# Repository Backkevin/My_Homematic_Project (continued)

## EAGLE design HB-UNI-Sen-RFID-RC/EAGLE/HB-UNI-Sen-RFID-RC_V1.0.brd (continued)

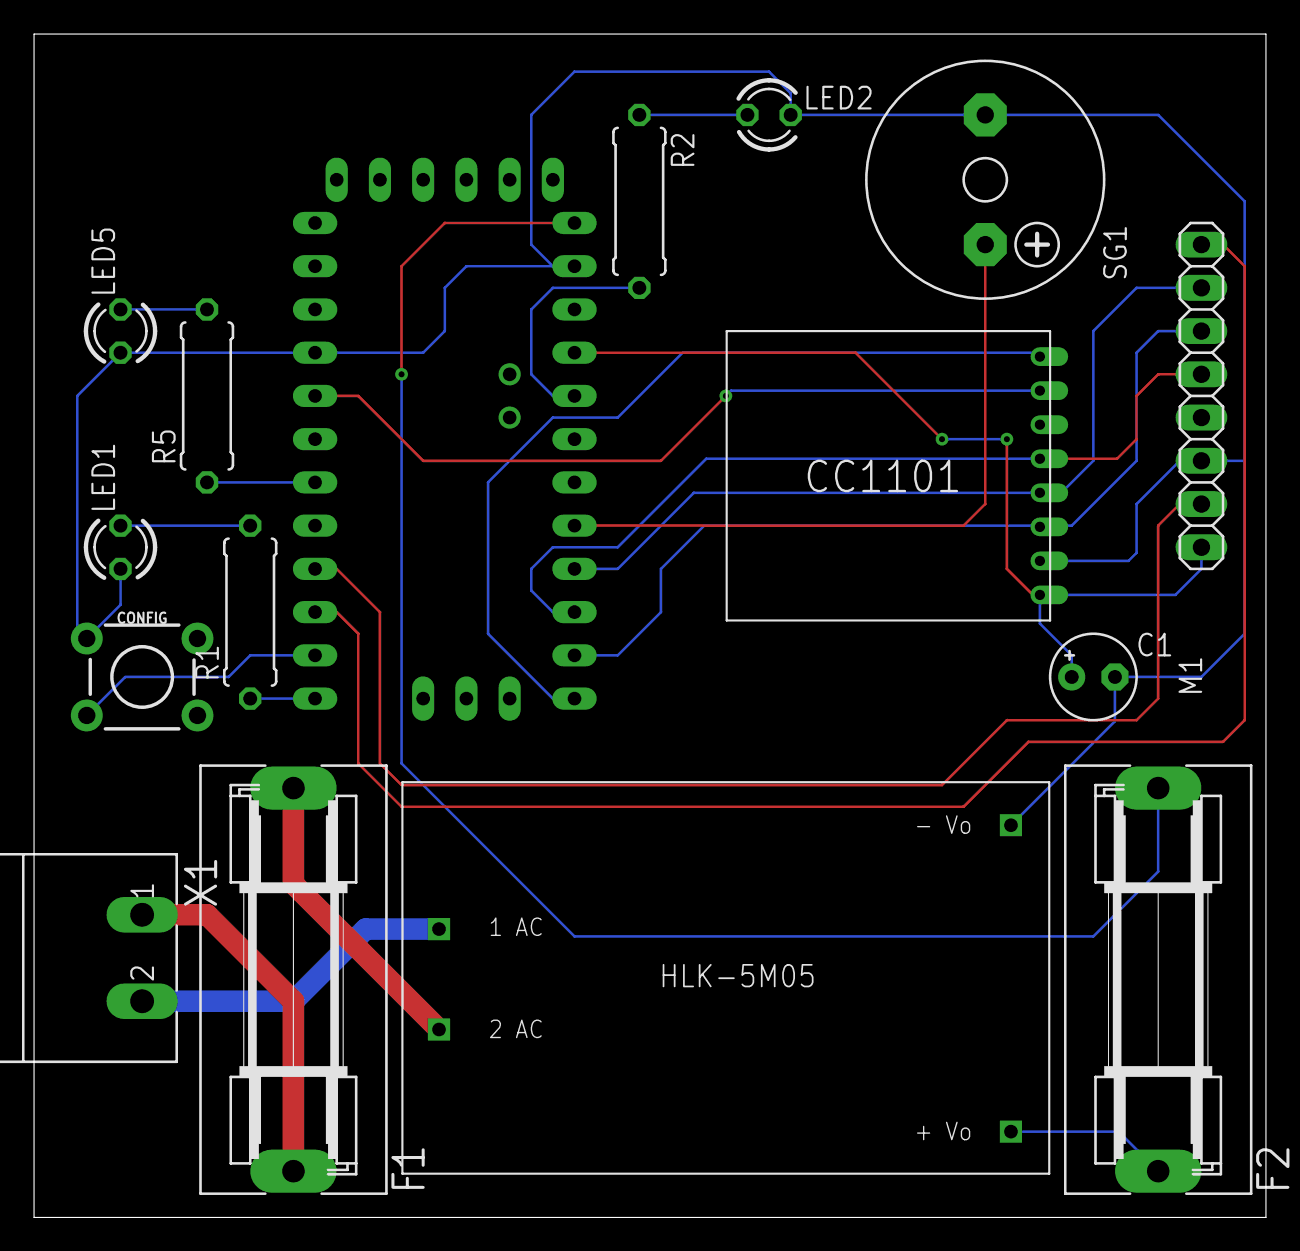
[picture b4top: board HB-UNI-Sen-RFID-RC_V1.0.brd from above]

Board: 2 copper layers, 72.4 x 69.5 mm, 16 parts (0 on the bottom side), 22 nets.

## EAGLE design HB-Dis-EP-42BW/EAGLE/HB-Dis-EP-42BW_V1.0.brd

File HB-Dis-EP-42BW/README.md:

# HB-Dis-EP-42BW
+ HB-Dis-EP-42BW
	+ V1.0
		* Work 50%
		* 230VAC Version
		* Partlist not OK
	+ Work in progress !

### Partslist 230VAC Version
                    
  Part Name   |      PIC      |   Part Info   | Part Quantity |   Part Link 
------------- | ------------- | ------------- | ------------- | -------------
Atmega1284||Atmega1284|1|[Links](https://de.aliexpress.com/item/33055132798.html?spm=a2g0o.productlist.0.0.77eb5e5fPvaMvS&algo_pvid=d8744989-b02e-473b-b5f8-e39dbb865ab2&algo_expid=d8744989-b02e-473b-b5f8-e39dbb865ab2-4&btsid=08f508f2-d514-42dc-8de8-63a7cc07db76&ws_ab_test=searchweb0_0,searchweb201602_2,searchweb201603_52)
CC1101||CC1101 Funkmodul|1|[Links](https://de.aliexpress.com/item/32924239954.html?spm=a2g0s.9042311.0.0.27424c4dO9ofu2)
Config,S1 - S8||Taster 6x6|9|[Links](https://de.aliexpress.com/item/32912263133.html?spm=a2g0s.9042311.0.0.2cb44c4dtuowdv)
LED1,LED2||LED 3mm|2|[Links](https://de.aliexpress.com/item/32844298998.html?spm=a2g0s.9042311.0.0.27424c4dBW9kvr)
HLK-5M05||HLK-PM01|1|[Links](https://de.aliexpress.com/item/32705471039.html?spm=a2g0s.9042311.0.0.2cb44c4dtuowdv)
F1,F2||Sicherungshalter|2|[Links](https://de.aliexpress.com/item/32817849786.html?spm=a2g0o.productlist.0.0.260073beDSkClD&algo_pvid=51b52a6f-dc94-4152-9721-98bffea40076&algo_expid=51b52a6f-dc94-4152-9721-98bffea40076-1&btsid=c94e558f-368d-470b-a49c-61c69230d3d9&ws_ab_test=searchweb0_0,searchweb201602_2,searchweb201603_52)
R1,R2||470 Ohm Widerstand|2|[Links](https://de.aliexpress.com/item/32475181535.html?spm=a2g0o.productlist.0.0.d4fa8034p2AKck&s=p&algo_pvid=4976c9e3-6165-4df4-b127-6d9845fdbe12&algo_expid=4976c9e3-6165-4df4-b127-6d9845fdbe12-1&btsid=7a52ff49-9ff4-47d2-965f-007ad481e8b7&ws_ab_test=searchweb0_0,searchweb201602_2,searchweb201603_52)
230V||Wannenstecker für AKL 249, 2-pol, RM5,08|1|[Links](https://www.reichelt.de/wannenstecker-fuer-akl-249-2-pol-rm5-08-akl-230-02-p36701.html?)
Arduino||Pin Header Streifen 12 Pin|2|[Links](https://de.aliexpress.com/item/32904918519.html?spm=a2g0s.9042311.0.0.27424c4dCsKCBi)
CC1101||Stiftleiste 20 polig, vergoldet, Raster 2,00mm|1|[Links](https://secure.reichelt.com/lu/de/stiftleiste-20-pol-vergoldet-bkl-10120400-p235635.html?)
C1||50V10UF|1|[Links](https://de.aliexpress.com/item/32741687066.html?spm=a2g0o.productlist.0.0.4d225216N68Cr1&algo_pvid=dbcb75f4-e623-4355-8aa4-ccd3a7b65d32&algo_expid=dbcb75f4-e623-4355-8aa4-ccd3a7b65d32-3&btsid=a9b8176e-1372-45d7-a781-8d3fc9fab8e5&ws_ab_test=searchweb0_0,searchweb201602_2,searchweb201603_52)
Arduino||Jumper|1|[Links](https://de.aliexpress.com/item/32873263301.html?spm=a2g0o.productlist.0.0.18ea263dluRsmQ&algo_pvid=b495ebad-e4de-4809-a086-8143c1f9f12b&algo_expid=b495ebad-e4de-4809-a086-8143c1f9f12b-2&btsid=53bb7c29-6fd7-4471-b8c4-bc2766b36d10&ws_ab_test=searchweb0_0,searchweb201602_2,searchweb201603_52)
Display||4,2 zoll color tinte bildschirm RSW|1|[Links](https://de.aliexpress.com/item/32960911279.html?spm=a2g0s.9042311.0.0.27424c4durraPx)
-|-|-|-
OPTIONAL||FT232RL USB zu TTL Serielle Adapter|1|[Links](https://de.aliexpress.com/item/32846166237.html?spm=a2g0s.9042311.0.0.27424c4dQGznlY)

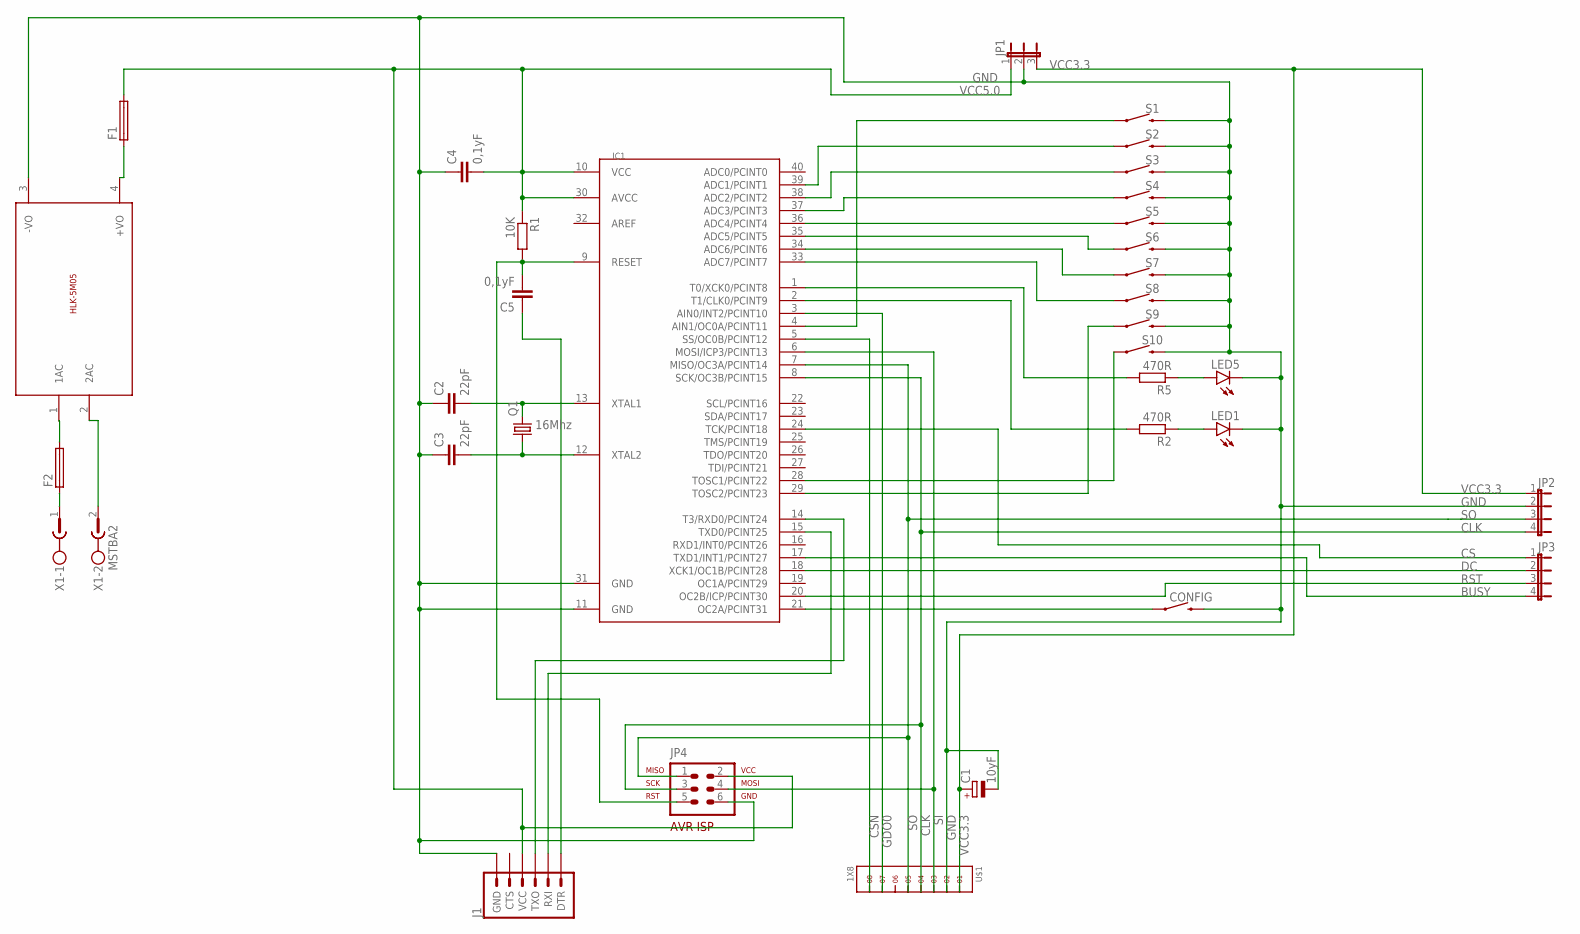
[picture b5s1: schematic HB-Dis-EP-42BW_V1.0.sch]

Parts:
C1: 10yF; E2,5-5
C2, C3: 22pF; C025-024X044
C4, C5: 0,1yF; C025-024X044
CONFIG: MOMENTARY-SWITCH-SPST-PTH-6.0MM-KIT; TACTILE_SWITCH_PTH_6.0MM_KIT
F1, F2: SH22,5A
IC1: MEGA1284P; DIL40
J1: 6_PIN_SERIAL_TARGETLONGPADS; 1X06_LONGPADS
JP1: JP2E; JP2
JP2, JP3: JP4E; JP4
JP4: AVR-ISP-6VERT; AVR-ISP-6
LED1, LED5: LED3MM
Q1: 16Mhz; HC49U-V
R1: 10K; 0309/10
R2, R5: 470R; 0309/10
S1, S2, S3, S4, S5, S6, S7, S8, S9, S10: MOMENTARY-SWITCH-SPST-PTH-6.0MM-KIT; TACTILE_SWITCH_PTH_6.0MM_KIT
U$1: 1X8
U$3: 5VDC/5W; HLK-5M05
X1: MSTBA2

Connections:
BUSY: IC1.17 (TXD1/INT1/PCINT27), JP3.4
CLK: IC1.8 (SCK/OC3B/PCINT15), JP2.4, JP4.3, U$1.4
CS: IC1.24 (TCK/PCINT18), JP3.1
CSN: IC1.5 (SS/OC0B/PCINT12), U$1.8
DC: IC1.18 (XCK1/OC1B/PCINT28), JP3.2
GDO0: IC1.3 (AIN0/INT2/PCINT10), U$1.7
GND: C1.-, C2.1, C3.1, C4.1, CONFIG.3 (2), IC1.11 (GND), IC1.31 (GND), J1.6 (GND), JP1.2, JP2.2, JP4.6, LED1.K (C), LED5.K (C), S1.3 (2), S2.3 (2), S3.3 (2), S4.3 (2), S5.3 (2), S6.3 (2), S7.3 (2), S8.3 (2), S9.3 (2), S10.3 (2), U$1.2, U$3.3 (-VO)
unnamed: C2.2, IC1.13 (XTAL1), Q1.2
unnamed: C3.2, IC1.12 (XTAL2), Q1.1
unnamed: C5.1, J1.1 (DTR)
unnamed: LED1.A, R2.1
unnamed: F2.1, X1.1
unnamed: U$3.2 (2AC), X1.2
unnamed: F2.2, U$3.1 (1AC)
unnamed: F1.1, U$3.4 (+VO)
unnamed: C5.2, IC1.9 (RESET), JP4.5, R1.2
unnamed: IC1.15 (TXD0/PCINT25), J1.2 (RXI)
unnamed: LED5.A, R5.1
unnamed: IC1.4 (AIN1/OC0A/PCINT11), S1.1
unnamed: IC1.14 (T3/RXD0/PCINT24), J1.3 (TXO)
unnamed: IC1.39 (ADC1/PCINT1), S2.1
unnamed: IC1.38 (ADC2/PCINT2), S3.1
unnamed: IC1.37 (ADC3/PCINT3), S4.1
unnamed: IC1.36 (ADC4/PCINT4), S5.1
unnamed: IC1.35 (ADC5/PCINT5), S6.1
unnamed: IC1.34 (ADC6/PCINT6), S7.1
unnamed: IC1.33 (ADC7/PCINT7), S8.1
unnamed: IC1.28 (TOSC1/PCINT22), S10.1
unnamed: IC1.29 (TOSC2/PCINT23), S9.1
unnamed: CONFIG.1, IC1.21 (OC2A/PCINT31)
unnamed: IC1.1 (T0/XCK0/PCINT8), R5.2
unnamed: IC1.2 (T1/CLK0/PCINT9), R2.2
RST: IC1.20 (OC2B/ICP/PCINT30), JP3.3
SI: IC1.6 (MOSI/ICP3/PCINT13), JP4.4, U$1.3
SO: IC1.7 (MISO/OC3A/PCINT14), JP2.3, JP4.1, U$1.5
VCC3.3: C1.+, JP1.3, JP2.1, U$1.1
VCC5.0: C4.2, F1.2, IC1.10 (VCC), IC1.30 (AVCC), J1.4 (VCC), JP1.1, JP4.2, R1.1

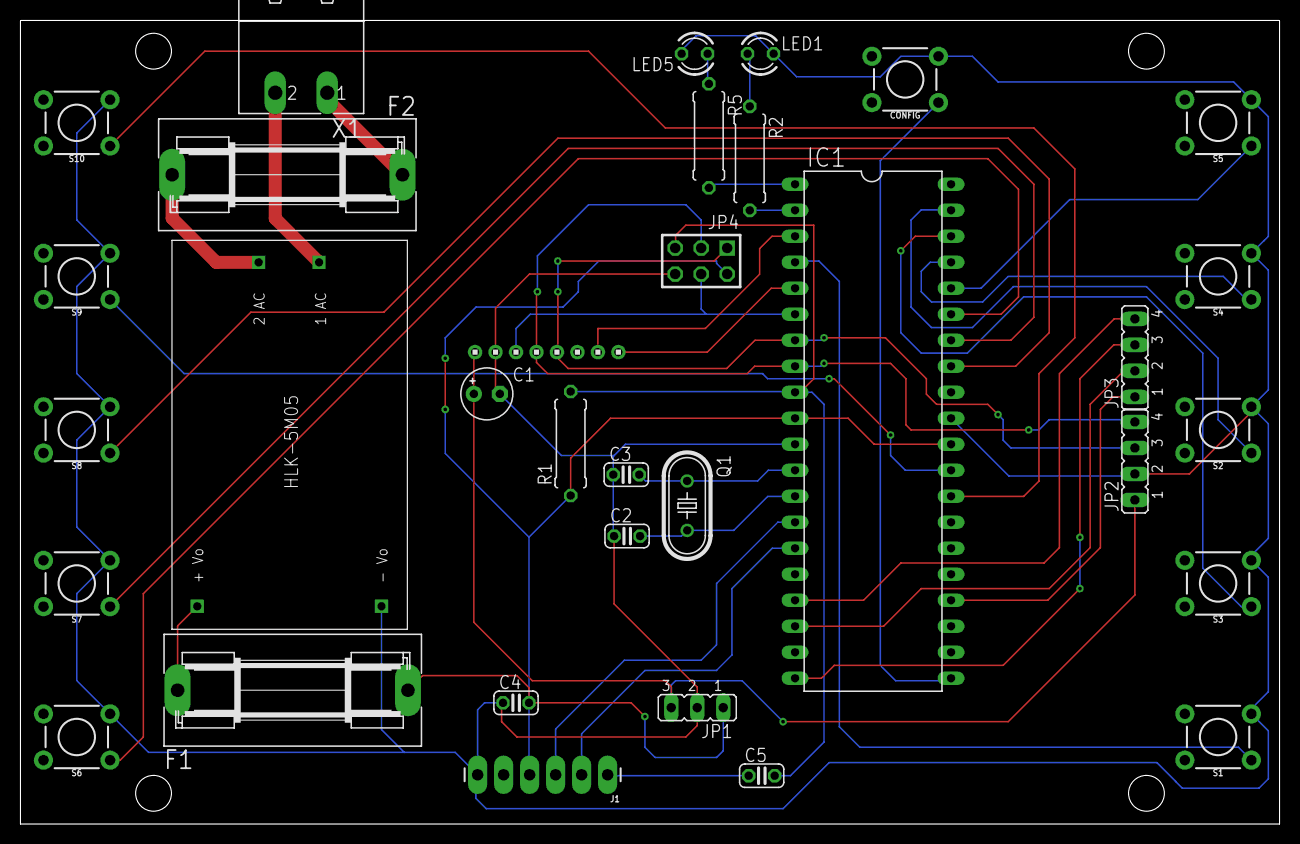
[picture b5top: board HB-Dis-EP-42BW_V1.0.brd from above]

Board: 2 copper layers, 123.0 x 78.5 mm, 33 parts (0 on the bottom side), 37 nets.

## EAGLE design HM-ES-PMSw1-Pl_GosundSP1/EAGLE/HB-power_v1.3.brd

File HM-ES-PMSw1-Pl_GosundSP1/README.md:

# HM-ES-PMSw1-Pl_GosundSP1

+ HM-ES-PMSw1-Pl_GosundSP1
	+ V1.3
		* Work 50%
		* 230VAC Version
		* Partlist not OK
	+ Work in progress !
>

### Partslist 230VAC Version
                    
  Part Name   |      PIC      |   Part Info   | Part Quantity |   Part Link 
------------- | ------------- | ------------- | ------------- | -------------
Atmega644||Atmega644|1|[Links](https://www.reichelt.de/mcu-atmega-avr-risc-64-kb-20-mhz-pdip-40-atmega-644-20-pu-p68173.html?&trstct=pos_0)
CC1101||CC1101 Funkmodul|1|[Links](https://de.aliexpress.com/item/32924239954.html?spm=a2g0s.9042311.0.0.27424c4dO9ofu2)
Config||Taster 6x6|1|[Links](https://de.aliexpress.com/item/32912263133.html?spm=a2g0s.9042311.0.0.2cb44c4dtuowdv)
LED1||LED 3mm|1|[Links](https://de.aliexpress.com/item/32844298998.html?spm=a2g0s.9042311.0.0.27424c4dBW9kvr)
HLK-5M05||HLK-PM01|1|[Links](https://de.aliexpress.com/item/32705471039.html?spm=a2g0s.9042311.0.0.2cb44c4dtuowdv)
F1,F2||Sicherungshalter|2|[Links](https://de.aliexpress.com/item/32817849786.html?spm=a2g0o.productlist.0.0.260073beDSkClD&algo_pvid=51b52a6f-dc94-4152-9721-98bffea40076&algo_expid=51b52a6f-dc94-4152-9721-98bffea40076-1&btsid=c94e558f-368d-470b-a49c-61c69230d3d9&ws_ab_test=searchweb0_0,searchweb201602_2,searchweb201603_52)
R1||470 Ohm Widerstand|1|[Links](https://de.aliexpress.com/item/32475181535.html?spm=a2g0o.productlist.0.0.d4fa8034p2AKck&s=p&algo_pvid=4976c9e3-6165-4df4-b127-6d9845fdbe12&algo_expid=4976c9e3-6165-4df4-b127-6d9845fdbe12-1&btsid=7a52ff49-9ff4-47d2-965f-007ad481e8b7&ws_ab_test=searchweb0_0,searchweb201602_2,searchweb201603_52)
230V||Wannenstecker für AKL 249, 2-pol, RM5,08|1|[Links](https://www.reichelt.de/wannenstecker-fuer-akl-249-2-pol-rm5-08-akl-230-02-p36701.html?)
RL1||Wannenstecker für AKL 249, 3-pol, RM5,08|1|[Links](https://www.reichelt.de/wannenstecker-fuer-akl-249-3-pol-rm5-08-akl-230-03-p36702.html?)
RL1||relais srd-05vdc|1|[Links](https://de.aliexpress.com/item/32695798177.html?spm=a2g0o.productlist.0.0.46db7659cuB4fB&algo_pvid=f16bd12e)
Arduino||Pin Header Streifen 12 Pin|2|[Links](https://de.aliexpress.com/item/32904918519.html?spm=a2g0s.9042311.0.0.27424c4dCsKCBi)
CC1101||Stiftleiste 20 polig, vergoldet, Raster 2,00mm|1|[Links](https://secure.reichelt.com/lu/de/stiftleiste-20-pol-vergoldet-bkl-10120400-p235635.html?)
C1||50V10UF|1|[Links](https://de.aliexpress.com/item/32741687066.html?spm=a2g0o.productlist.0.0.4d225216N68Cr1&algo_pvid=dbcb75f4-e623-4355-8aa4-ccd3a7b65d32&algo_expid=dbcb75f4-e623-4355-8aa4-ccd3a7b65d32-3&btsid=a9b8176e-1372-45d7-a781-8d3fc9fab8e5&ws_ab_test=searchweb0_0,searchweb201602_2,searchweb201603_52)
Arduino||Jumper|1|[Links](https://de.aliexpress.com/item/32873263301.html?spm=a2g0o.productlist.0.0.18ea263dluRsmQ&algo_pvid=b495ebad-e4de-4809-a086-8143c1f9f12b&algo_expid=b495ebad-e4de-4809-a086-8143c1f9f12b-2&btsid=53bb7c29-6fd7-4471-b8c4-bc2766b36d10&ws_ab_test=searchweb0_0,searchweb201602_2,searchweb201603_52)
MessW||widerstand 2512 SMD|1|[Links](https://de.aliexpress.com/item/32368758351.html?spm=a2g0s.9042311.0.0.27424c4dBh27Vw)
HLW8012||HLW8012|1|[Links](https://de.aliexpress.com/item/4000044416257.html?spm=a2g0s.9042311.0.0.27424c4dBh27Vw)
Step-Down||DC Step-Down-Schritt-Up Konverter|1|[Links](https://de.aliexpress.com/item/32814821312.html?spm=a2g0s.9042311.0.0.27424c4dikfDji)
-|-|-|-
OPTIONAL||FT232RL USB zu TTL Serielle Adapter|1|[Links](https://de.aliexpress.com/item/32846166237.html?spm=a2g0s.9042311.0.0.27424c4dQGznlY)

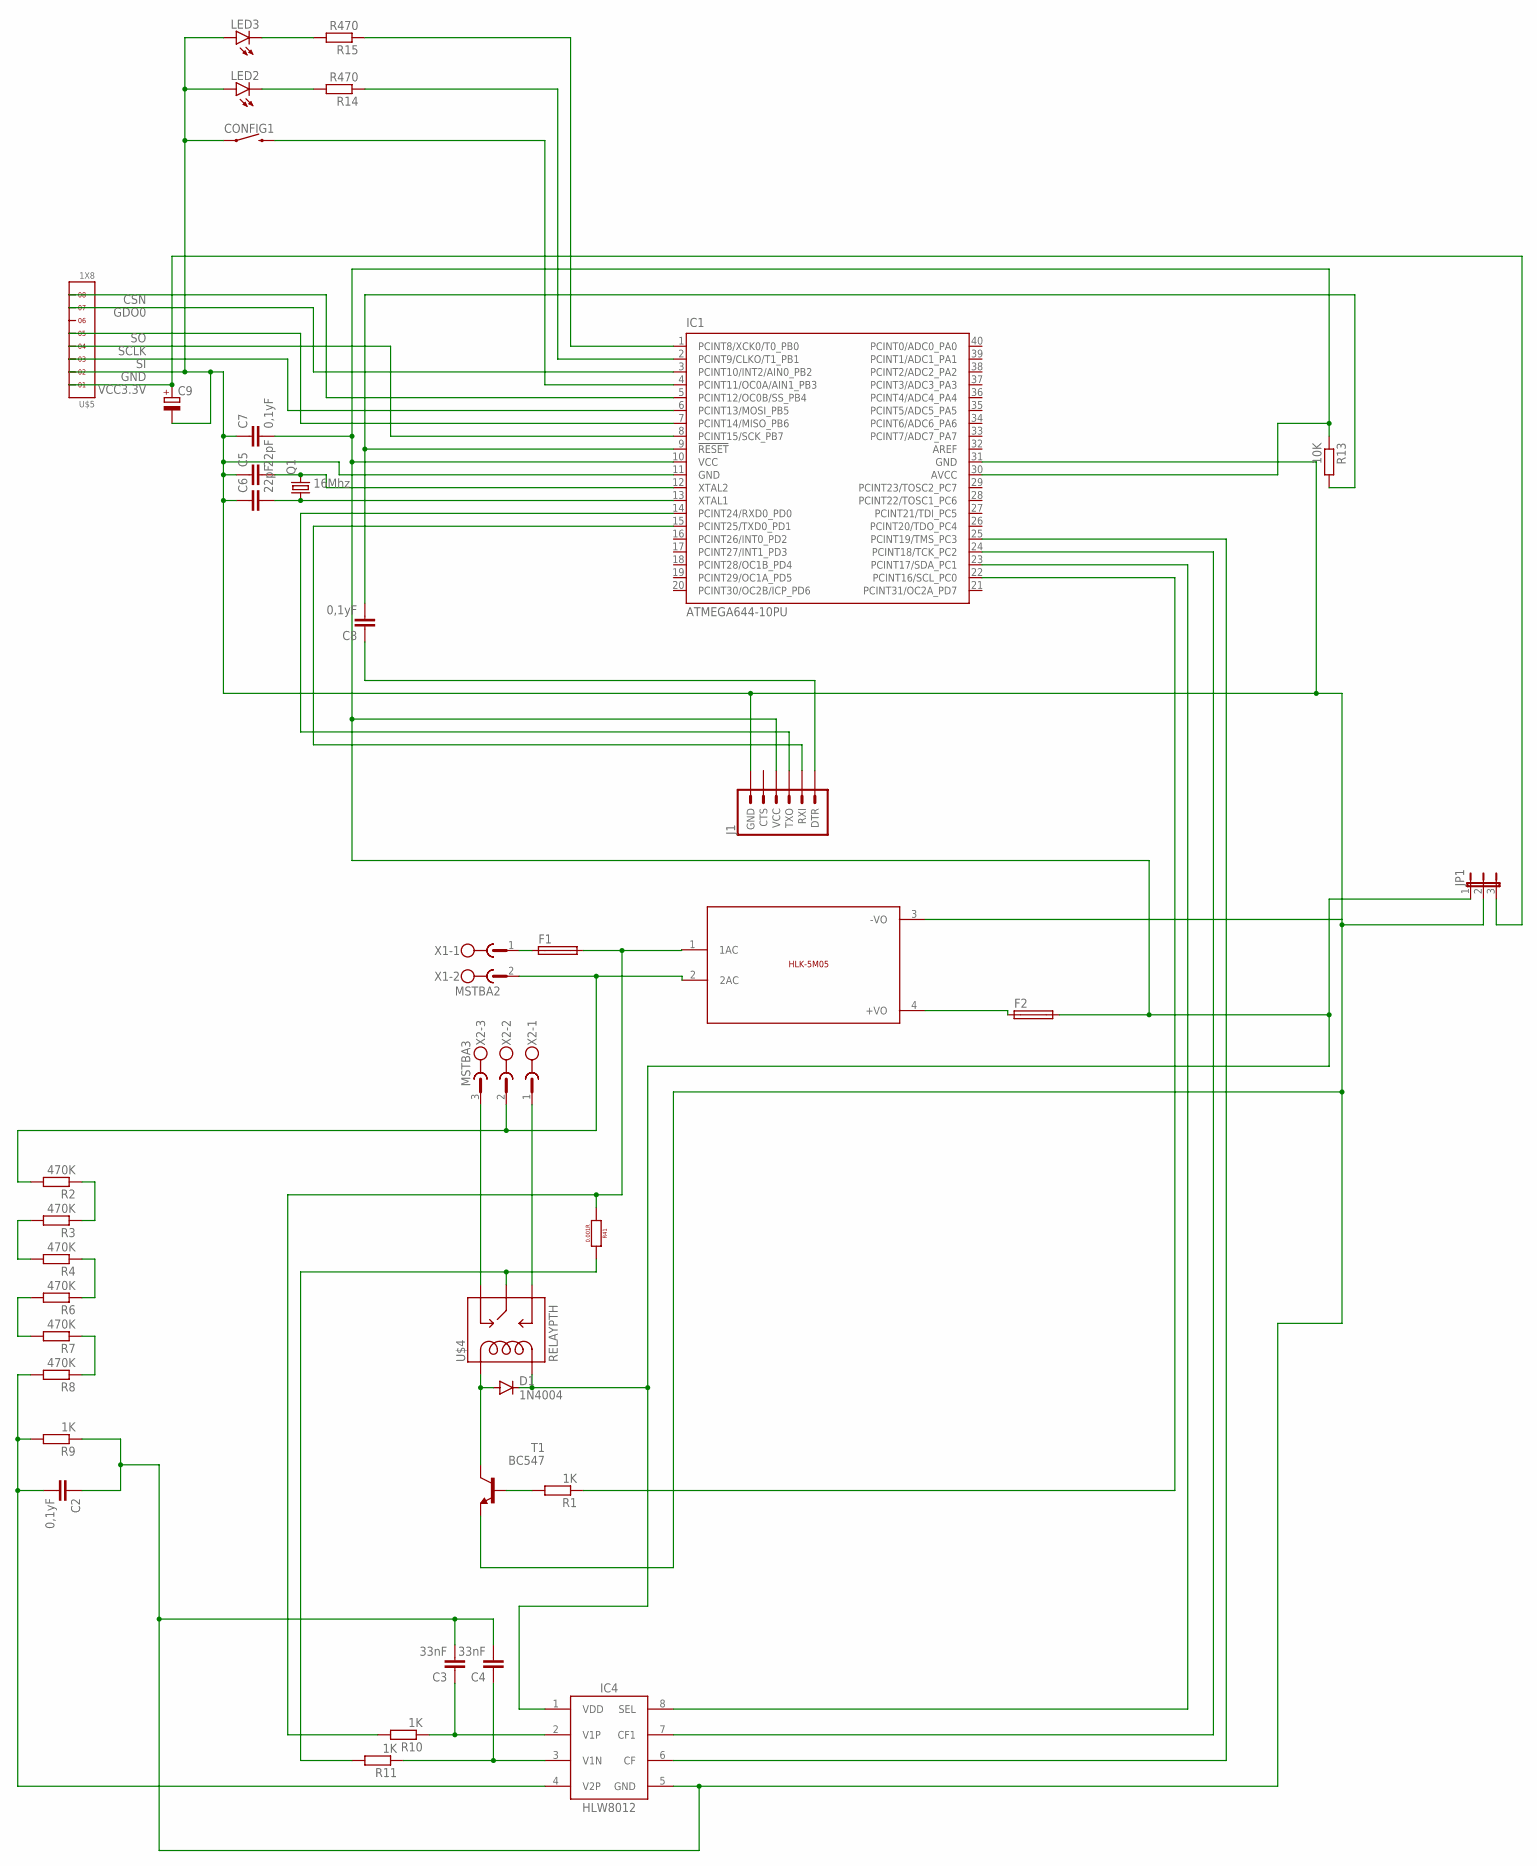
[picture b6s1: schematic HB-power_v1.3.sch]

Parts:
C2: 0,1yF; C050-024X044
C3, C4: 33nF; C050-024X044
C5, C6: 22pF; C025-024X044
C7, C8: 0,1yF; C025-024X044
C9: CPOL-EUE2.5-5; E2,5-5
CONFIG1: MOMENTARY-SWITCH-SPST-PTH-6.0MM-KIT; TACTILE_SWITCH_PTH_6.0MM_KIT
D1: 1N4004; DO41-10
F1, F2: SH22,5A
IC1: ATMEGA644-10PU; DIL40
IC4: HLW8012; SOP8
J1: 6_PIN_SERIAL_TARGETLONGPADS; 1X06_LONGPADS
JP1: JP2E; JP2
LED2, LED3: LED3MM
Q1: 16Mhz; HC49U-V
R1, R9, R10, R11: 1K; 0309/10
R2, R3, R4, R6, R7, R8: 470K; 0309/10
R13: 10K; 0309/10
R14, R15: R470; 0309/10
R41: 0.001R; 2512
T1: BC547; TO92
U$3: 5VDC/5W; HLK-5M05
U$4: RELAYPTH; SRD-05VDC-SL-C
U$5: 1X8
X1: MSTBA2
X2: MSTBA3

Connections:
CSN: IC1.5 (PCINT12/OC0B/SS_PB4), U$5.8
GDO0: IC1.3 (PCINT10/INT2/AIN0_PB2), U$5.7
GND: C2.1, C3.2, C4.2, C5.1, C6.1, C7.1, C9.-, CONFIG1.1, IC1.11 (GND), IC1.31 (GND), IC4.5 (GND), J1.6 (GND), JP1.2, LED2.A, LED3.A, R9.1, T1.1 (E), U$3.3 (-VO), U$5.2; also elsewhere on the board
L: F1.1, X1.1
L1: F1.2, R10.2, R41.1, U$3.1 (1AC)
L2: R11.2, R41.2, U$4.SWCOMMON
N: R2.2, U$3.2 (2AC), X1.2, X2.2
unnamed: D1.A, T1.3 (C), U$4.COIL1
unnamed: R1.2, T1.2 (B)
unnamed: IC1.22 (PCINT16/SCL_PC0), R1.1
unnamed: IC1.23 (PCINT17/SDA_PC1), IC4.8 (SEL)
unnamed: IC1.24 (PCINT18/TCK_PC2), IC4.7 (CF1)
unnamed: IC1.25 (PCINT19/TMS_PC3), IC4.6 (CF)
unnamed: C5.2, IC1.12 (XTAL2), Q1.2
unnamed: F2.1, U$3.4 (+VO)
unnamed: U$4.SWCLOSED (SWCLOSE), X2.3
unnamed: U$4.SWOPEN, X2.1
unnamed: R2.1, R3.1
unnamed: R4.1, R6.1
unnamed: R7.1, R8.1
unnamed: R3.2, R4.2
unnamed: R6.2, R7.2
unnamed: C2.2, IC4.4 (V2P), R8.2, R9.2
unnamed: C6.2, IC1.13 (XTAL1), Q1.1
unnamed: C3.1, IC4.2 (V1P), R10.1
unnamed: C8.1, J1.1 (DTR)
unnamed: C4.1, IC4.3 (V1N), R11.1
unnamed 27: C7.2, D1.C, F2.2, IC1.10 (VCC), IC1.30 (AVCC), IC4.1 (VDD), J1.4 (VCC), JP1.1, R13.1, U$4.COIL0; also elsewhere on the board
unnamed 28: C8.2, IC1.9 (!RESET), R13.2; also elsewhere on the board
unnamed: CONFIG1.3 (2), IC1.4 (PCINT11/OC0A/AIN1_PB3)
unnamed: IC1.14 (PCINT24/RXD0_PD0), J1.3 (TXO)
unnamed: IC1.15 (PCINT25/TXD0_PD1), J1.2 (RXI)
unnamed: LED2.K (C), R14.2
unnamed: LED3.K (C), R15.2
unnamed: IC1.2 (PCINT9/CLKO/T1_PB1), R14.1
unnamed: IC1.1 (PCINT8/XCK0/T0_PB0), R15.1
SCLK: IC1.8 (PCINT15/SCK_PB7), U$5.4; also elsewhere on the board
SI: IC1.6 (PCINT13/MOSI_PB5), U$5.3; also elsewhere on the board
SO: IC1.7 (PCINT14/MISO_PB6), U$5.5; also elsewhere on the board
VCC3.3V: C9.+, JP1.3, U$5.1

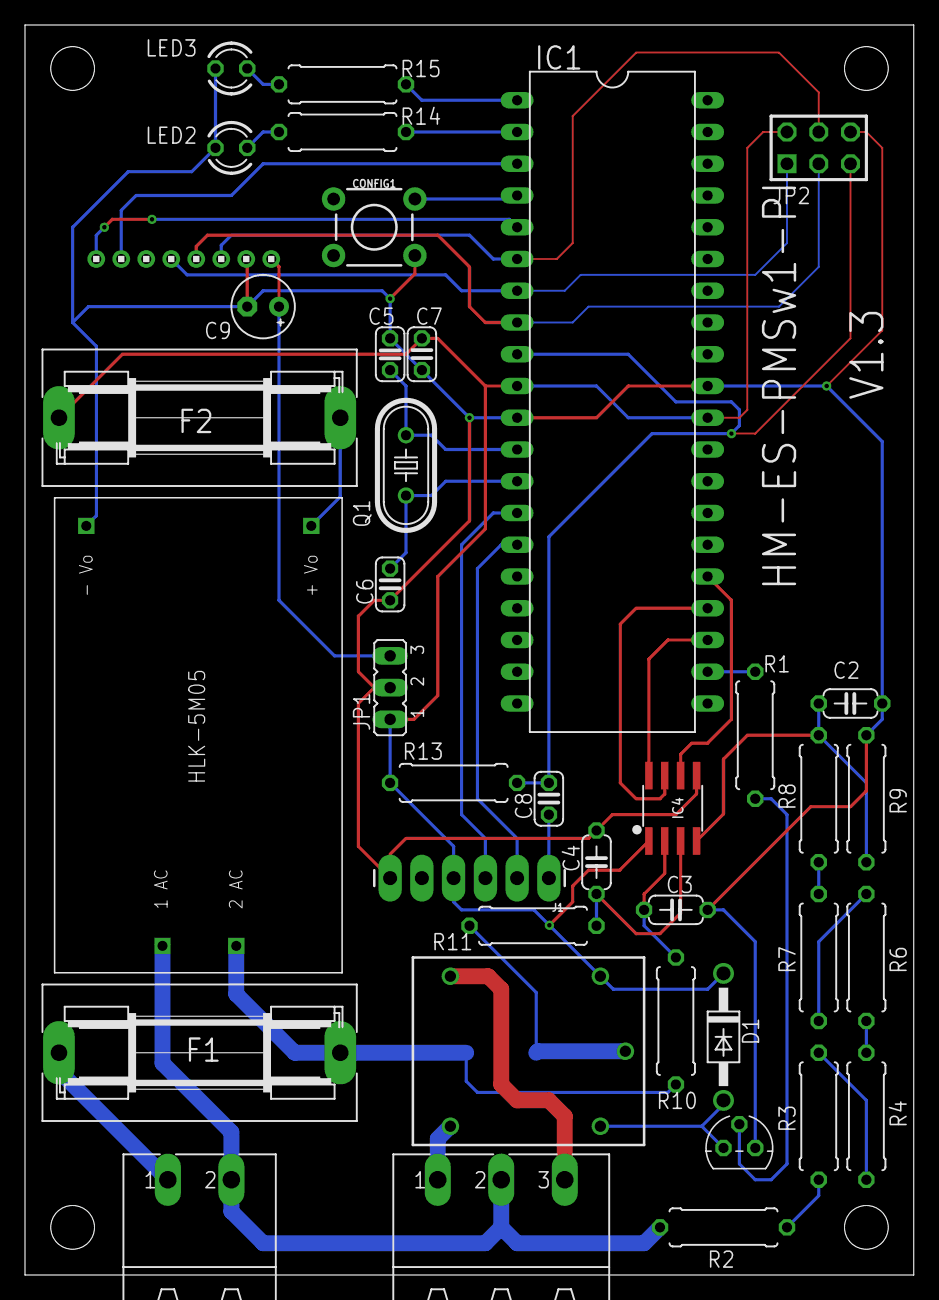
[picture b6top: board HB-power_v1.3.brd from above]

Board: 2 copper layers, 71.1 x 100.0 mm, 40 parts (1 on the bottom side), 40 nets.

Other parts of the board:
JP2: AVR-ISP-6VERT; AVR-ISP-6

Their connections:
GND: JP2.6; also elsewhere on the board
unnamed 27: JP2.2; also elsewhere on the board
unnamed 28: JP2.5; also elsewhere on the board
SCLK: JP2.3; also elsewhere on the board
SI: JP2.4; also elsewhere on the board
SO: JP2.1; also elsewhere on the board

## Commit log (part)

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2019-09-09 Create .s#1
2019-09-13 Update issue templates
